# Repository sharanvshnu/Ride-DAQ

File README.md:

# RideDAQ
### Electric Scooter Ride Quality & Data Acquisition System

<p align="center">
  <b>Capture. Analyse. Predict.</b><br>
  An embedded data-acquisition platform for electric-scooter ride-quality monitoring and predictive-maintenance research.
</p>

---

## 01. Overview

**RideDAQ** is an embedded scooter-monitoring and data-acquisition system intended to capture riding dynamics, vibration, positional information and environmental parameters. The platform combines inertial sensing, GNSS, local data logging and wireless connectivity.

The longer-term objective is to study ride quality, identify abnormal vibration patterns and investigate data-driven maintenance indicators. These are development goals, not validated capabilities at this stage.

## 02. System Architecture

```mermaid
flowchart TB
    Scooter["Electric scooter"] --> Unit["RideDAQ acquisition unit"]
    subgraph Unit
      MCU["Teensy 4.0"]
      IMU["BMI323 IMU"] --> MCU
      GNSS["GP-02 GNSS"] --> MCU
      ENV["BME280"] --> MCU
      RTC["DS3231M RTC"] --> MCU
      EEPROM["I²C EEPROM — exact part to be confirmed"] <--> MCU
      MCU --> SD["MicroSD storage"]
      MCU <--> BLE["HM-10 BLE"]
    end
    BLE <--> Phone["Mobile / BLE interface"]
    SD --> Analysis["Offline data analysis"]
    Analysis --> Quality["Ride-quality assessment"]
    Analysis --> Maintenance["Predictive-maintenance research"]
```

## 03. Hardware

| Subsystem | Component / implementation | Role |
|---|---|---|
| Main controller | Teensy 4.0 | Acquisition and control |
| Inertial sensing | BMI323 6-DOF IMU breakout | Acceleration and angular velocity |
| Positioning | GP-02 GNSS module | Position and timing data |
| Environmental sensing | BME280 | Temperature, humidity and pressure |
| Real-time clock | DS3231M | Timestamp reference |
| Non-volatile memory | I²C EEPROM — part number requires reconciliation | Configuration / persistent data |
| Data logging | microSD | Local ride-data storage |
| Wireless interface | HM-10 BLE module | Wireless communication |
| Power | TPS5430 buck and LD1117S33 LDO in the current design | 5 V and 3.3 V rails |

**Important design note:** the current project files and earlier design notes disagree on the EEPROM part number (AT24CS32 versus AT24C512). The exact fitted/selected device must be confirmed before the BOM and firmware address map are treated as final.

## 04. Interfaces

| Interface | Intended peripherals |
|---|---|
| I²C | BMI323, BME280, DS3231M and EEPROM |
| SPI2 | microSD |
| UART2 | HM-10 BLE |
| UART3 | GP-02 GNSS |
| ADC | Battery-voltage sensing (planned / verify schematic connectivity) |
| GPIO | Status LEDs and GNSS PPS |

Pin assignments and hierarchical sheet connectivity remain subject to schematic review. Refer to the current KiCad design files rather than treating this summary as a pin-level sign-off.

## 05. Power Architecture

The current design uses a nominal 2S Li-ion battery input (6.0–8.4 V design range), input protection, a TPS5430-based 5 V buck stage and an LD1117S33 3.3 V LDO stage.

```mermaid
flowchart LR
  BAT["2S battery<br/>6.0–8.4 V"] --> PROT["Input protection"]
  PROT --> BUCK["TPS5430 buck<br/>5 V"]
  BUCK --> TEENSY["Teensy 4.0"]
  BUCK --> LDO["LD1117S33"]
  LDO --> RAIL["3.3 V peripherals"]
```

The power-stage component selection, low-input regulation margin, capacitor suitability, transient protection and thermal performance still require engineering verification. This block diagram describes the intended architecture, not a validated power-stage sign-off.

## 06. Development Status

| Workstream | Status |
|---|---|
| System architecture | Defined; under review |
| KiCad schematic | Created; electrical review pending |
| PCB placement / routing | In development; verify current board state |
| Firmware | Planned / in development |
| Sensor integration | Planned |
| SD data logging | Planned |
| BLE communication | Planned |
| Scooter pilot | Planned |
| Ride-quality analysis | Future work |
| Predictive-maintenance modelling | Future research |

## 07. Pilot Objectives

The initial pilot is intended to collect real-world scooter data and explore:

- Road-induced vibration characteristics
- Acceleration and movement patterns
- Ride-condition classification
- Abnormal vibration signatures
- Operational trends and potential maintenance indicators

No predictive-maintenance performance is claimed until supported by collected data and validated analysis.

## 08. Repository Structure

```text
RideDAQ/
├── v1/
│   ├── Hardware/
│   │   └── RideDAQ_KiCad/
│   │       └── RideDAQ_v1/
│   │           ├── RideDAQ_v1.kicad_pro
│   │           ├── RideDAQ_v1.kicad_sch
│   │           ├── RideDAQ_v1.kicad_pcb
│   │           ├── Sheets/
│   │           └── Libraries/
│   ├── Firmware/
│   └── Documentation/
├── README.md
└── .gitignore
```

The Firmware and Documentation directories will be populated as those workstreams mature.

## 09. Toolchain

- **Embedded platform:** Teensy 4.0
- **Firmware:** C / C++
- **Hardware design:** KiCad
- **Interfaces:** I²C, SPI, UART and BLE
- **Analysis:** Python (planned)

## 10. Engineering Gate Before PCB Release

Before manufacturing, complete and record:

1. Hierarchical schematic connectivity review.
2. Reconciliation of component MPNs, values, footprints and BOM.
3. Power-stage calculations and datasheet checks.
4. KiCad ERC with all errors reviewed.
5. Schematic-to-PCB consistency check.
6. Footprint, 3D model and connector-mechanical review.
7. PCB routing, copper zones and DRC.
8. Manufacturing-output review.

A successful Git push or a visually complete schematic/PCB is not evidence that ERC, DRC or electrical validation has passed.

---

**RideDAQ — Capture real-world data. Understand vehicle behaviour. Explore predictive maintenance.**

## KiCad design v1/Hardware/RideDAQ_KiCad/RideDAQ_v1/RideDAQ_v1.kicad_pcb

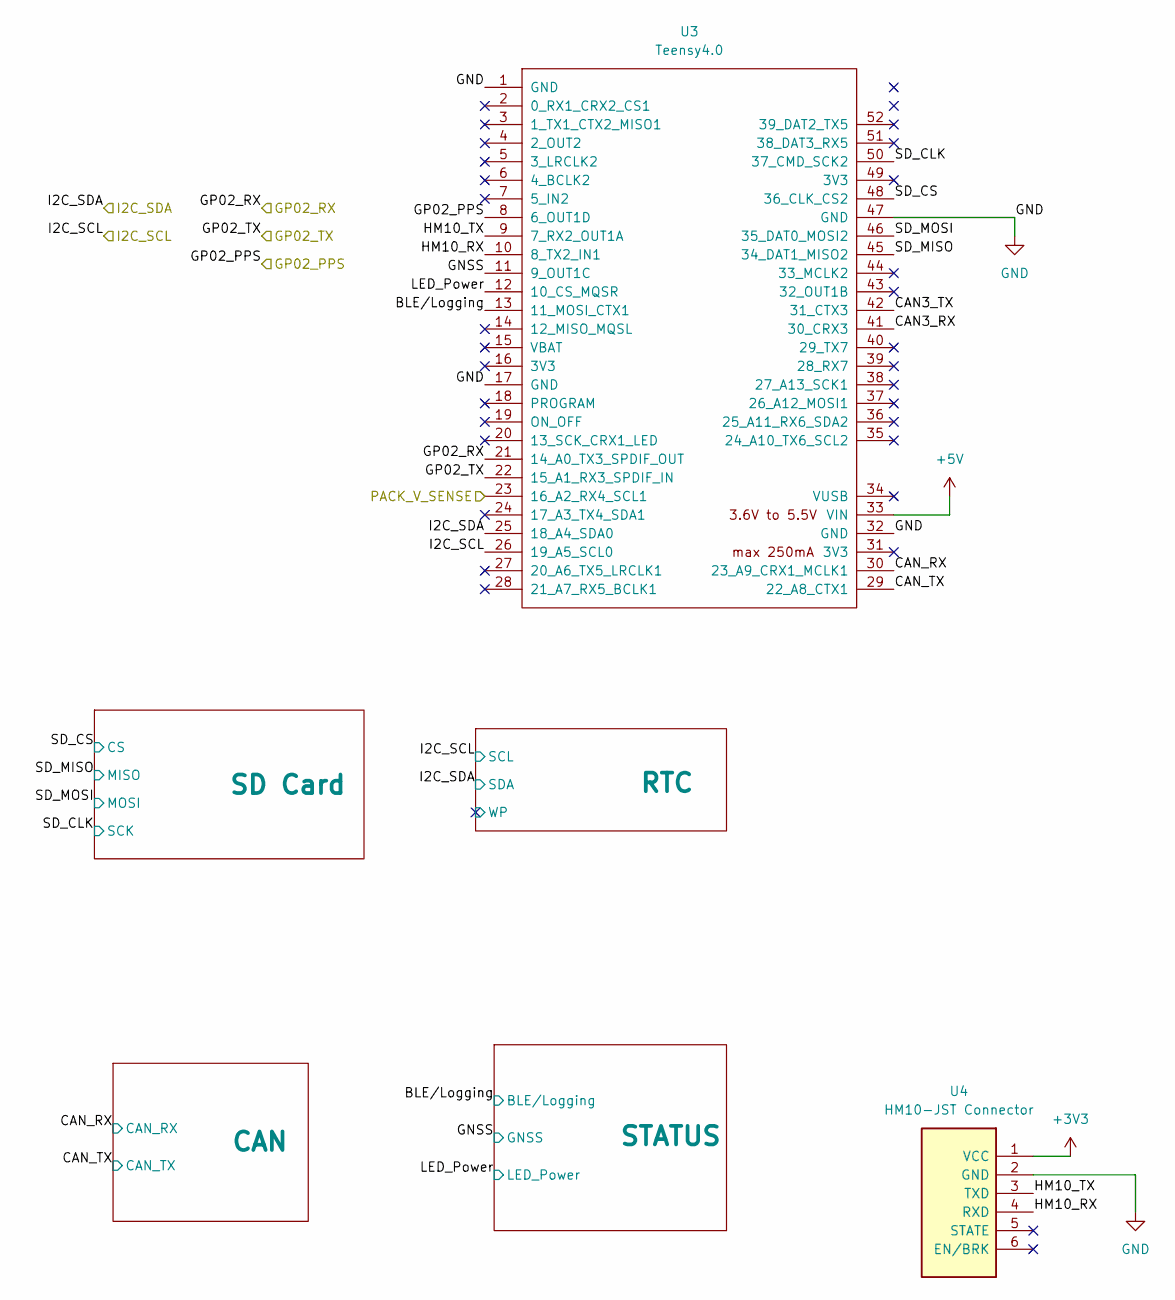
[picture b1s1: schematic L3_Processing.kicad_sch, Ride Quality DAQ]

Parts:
U3: Teensy4.0; Teensy40_All_Pins
U4: HM10-JST Connector; Molex_CLIK-Mate_502382-0670_1x06-1MP_P1.25mm_Vertical

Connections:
+3V3: U4.1 (VCC); also elsewhere on the board
+5V: U3.33 (VIN); also elsewhere on the board
/L2_Power_Conditioning/PACK_V_SENSE: U3.23 (16_A2_RX4_SCL1); also elsewhere on the board
/L3_Processing/BLE/Logging: U3.13 (11_MOSI_CTX1); also elsewhere on the board
/L3_Processing/CAN3_RX: U3.41 (30_CRX3)
/L3_Processing/CAN3_TX: U3.42 (31_CTX3)
/L3_Processing/CAN_RX: U3.30 (23_A9_CRX1_MCLK1); also elsewhere on the board
/L3_Processing/CAN_TX: U3.29 (22_A8_CTX1); also elsewhere on the board
/L3_Processing/GNSS: U3.11 (9_OUT1C); also elsewhere on the board
/L3_Processing/GP02_PPS: U3.8 (6_OUT1D); also elsewhere on the board
/L3_Processing/GP02_RX: U3.21 (14_A0_TX3_SPDIF_OUT); also elsewhere on the board
/L3_Processing/GP02_TX: U3.22 (15_A1_RX3_SPDIF_IN); also elsewhere on the board
/L3_Processing/HM10_RX: U3.10 (8_TX2_IN1), U4.4 (RXD)
/L3_Processing/HM10_TX: U3.9 (7_RX2_OUT1A), U4.3 (TXD)
/L3_Processing/I2C_SCL: U3.26 (19_A5_SCL0); also elsewhere on the board
/L3_Processing/I2C_SDA: U3.25 (18_A4_SDA0); also elsewhere on the board
/L3_Processing/LED_Power: U3.12 (10_CS_MQSR); also elsewhere on the board
/L3_Processing/SD_CLK: U3.50 (37_CMD_SCK2); also elsewhere on the board
/L3_Processing/SD_CS: U3.48 (36_CLK_CS2); also elsewhere on the board
/L3_Processing/SD_MISO: U3.45 (34_DAT1_MISO2); also elsewhere on the board
/L3_Processing/SD_MOSI: U3.46 (35_DAT0_MOSI2); also elsewhere on the board
GND: U3.1 (GND), U3.17 (GND), U3.32 (GND), U3.47 (GND), U4.2 (GND); also elsewhere on the board

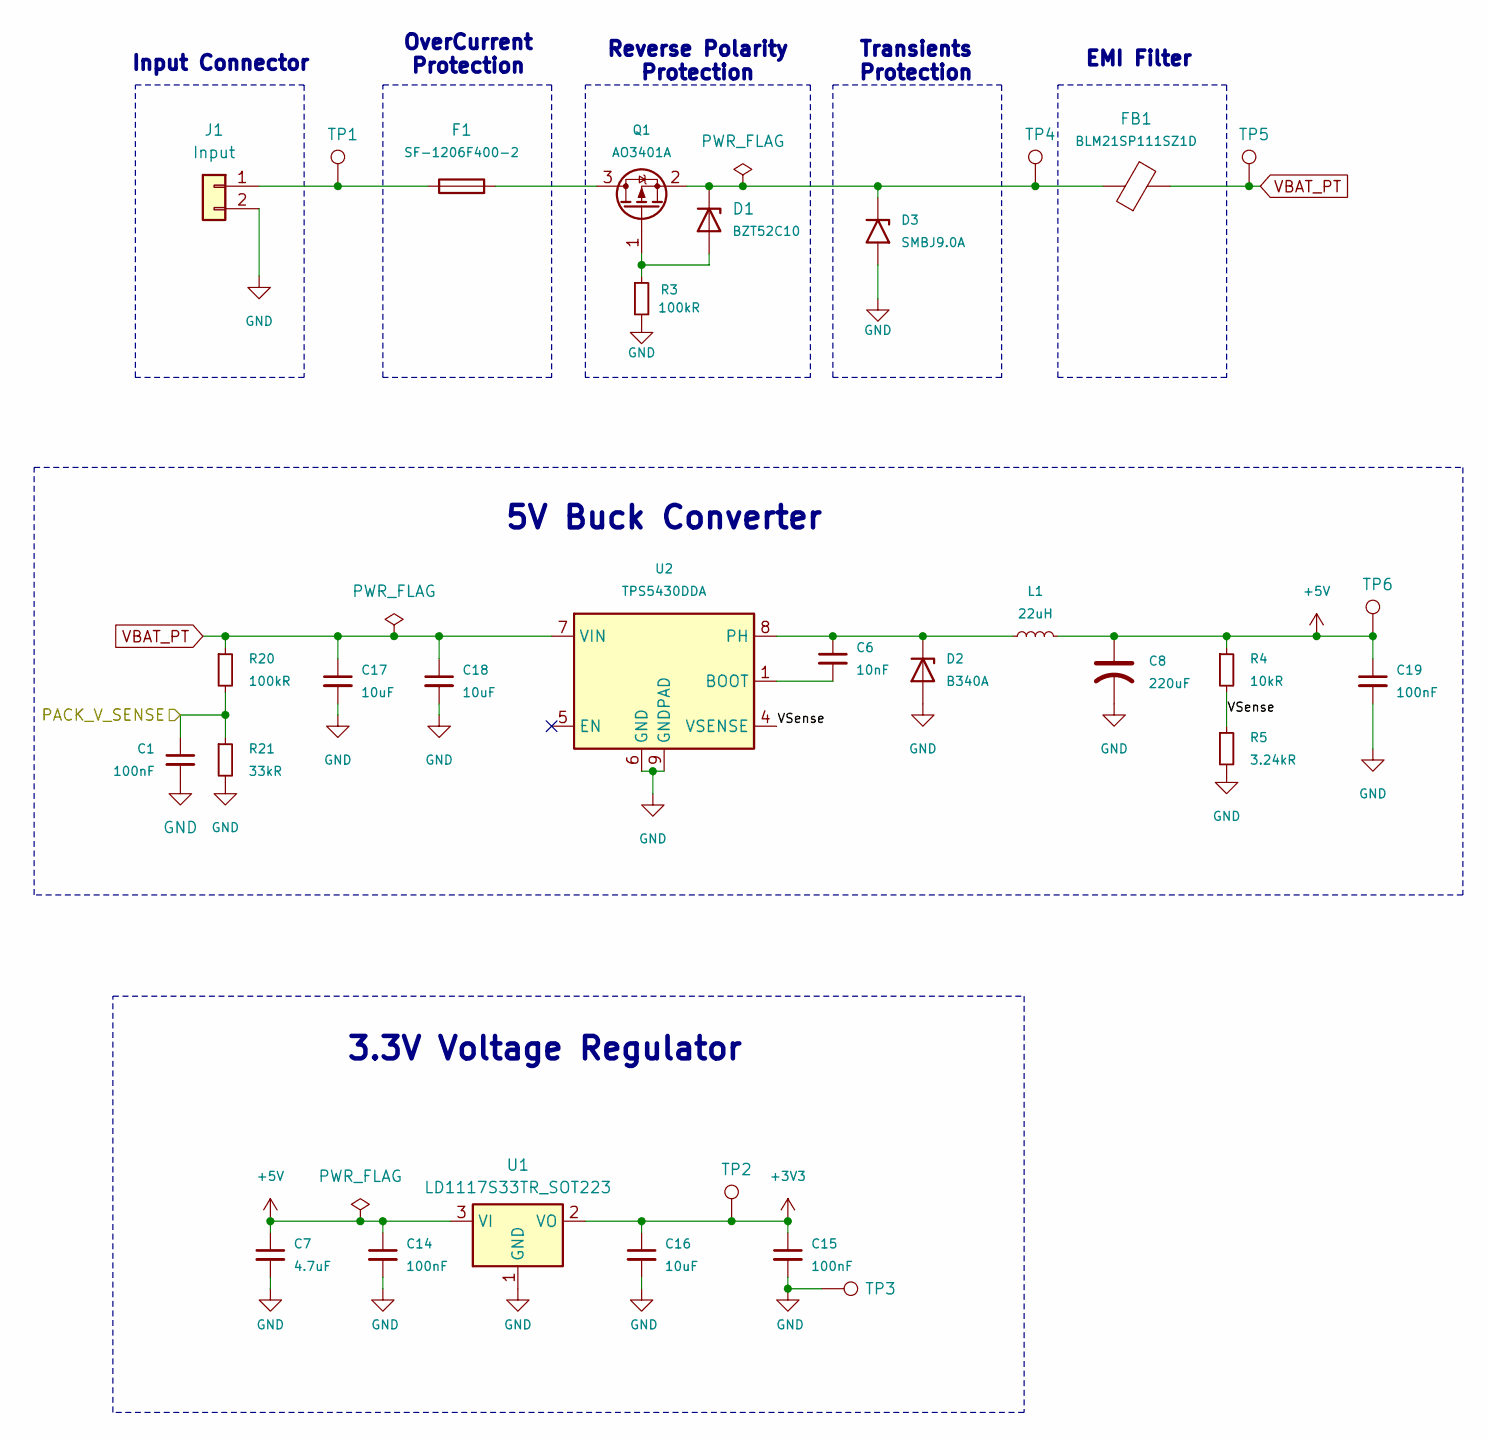
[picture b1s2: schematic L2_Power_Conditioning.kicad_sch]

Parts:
C1: 100nF; C_0805_2012Metric
C6: 10nF; C_0805_2012Metric; MPN CC0805KRX7R9BB103
C7: 4.7uF; C_0805_2012Metric; MPN TCC0805X7R475K500FT
C8: 220uF; CP_EIA-7343-31_Kemet-D; MPN UUD1C101MCL1GS
C14, C15, C19: 100nF; C_0805_2012Metric; MPN CC0805KKX7R0BB104
C16, C17, C18: 10uF; C_0805_2012Metric; MPN CL21B106KOQNNNE
D1: BZT52C10; D_SOD-123
D2: B340A; D_SMA; MPN B340A-E3/61T
D3: SMBJ9.0A; D_SMB
F1: SF-1206F400-2; Fuse_1206_3216Metric_Pad1.42x1.75mm_HandSolder
FB1: BLM21SP111SZ1D; L_0805_2012Metric
J1: Input; JST_EH_B2B-EH-A_1x02_P2.50mm_Vertical
L1: 22uH; L_12x12mm_H8mm
Q1: AO3401A; SOT-23W
R3: 100kR; R_0805_2012Metric; MPN 0805W8F1003T5E
R4: 10kR; R_0805_2012Metric; MPN RC0805FR-0710KL
R5: 3.24kR; R_0805_2012Metric; MPN 0603WAF3241T5E
R20: 100kR; R_0805_2012Metric; MPN RC0805FR-0710KL
R21: 33kR; R_0805_2012Metric; MPN 0603WAF3241T5E
TP1, TP2, TP3, TP4, TP5, TP6: TestPoint; TestPoint_Pad_D1.5mm
U1: LD1117S33TR_SOT223; SOT-223-3_TabPin2; MPN LD1117S33CTR
U2: TPS5430DDA; TI_SO-PowerPAD-8_ThermalVias

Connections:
+3V3: C15.1, C16.1, TP2.1 (1_1), U1.2 (VO); also elsewhere on the board
+5V: C7.1, C8.1, C14.1, C19.1, L1.2, R4.1, TP6.1 (1_1), U1.3 (VI); also elsewhere on the board
/L2_Power_Conditioning/PACK_V_SENSE: C1.1, R20.2, R21.1; also elsewhere on the board
/L2_Power_Conditioning/VSense: R4.2, R5.1, U2.4 (VSENSE)
GND: C1.2, C7.2, C8.2, C14.2, C15.2, C16.2, C17.2, C18.2, C19.2, D2.2 (A), D3.2 (A2), J1.2, R3.2, R5.2, R21.2, TP3.1 (1_1), U1.1 (GND), U2.6 (GND), U2.9 (GNDPAD); also elsewhere on the board
unnamed: D1.2 (A), Q1.1 (G), R3.1
unnamed: D1.1 (K), D3.1 (A1), FB1.1, Q1.2 (S), TP4.1 (1_1)
unnamed: C6.1, D2.1 (K), L1.1, U2.8 (PH)
unnamed: F1.1, J1.1, TP1.1 (1_1)
unnamed: F1.2, Q1.3 (D)
unnamed: C6.2, U2.1 (BOOT)
VBAT_PT: C17.1, C18.1, FB1.2, R20.1, TP5.1 (1_1), U2.7 (VIN)

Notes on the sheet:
Reverse Polarity Protection
Input Connector
5V Buck Converter
Transients Protection
3.3V Voltage Regulator
EMI Filter
OverCurrent Protection

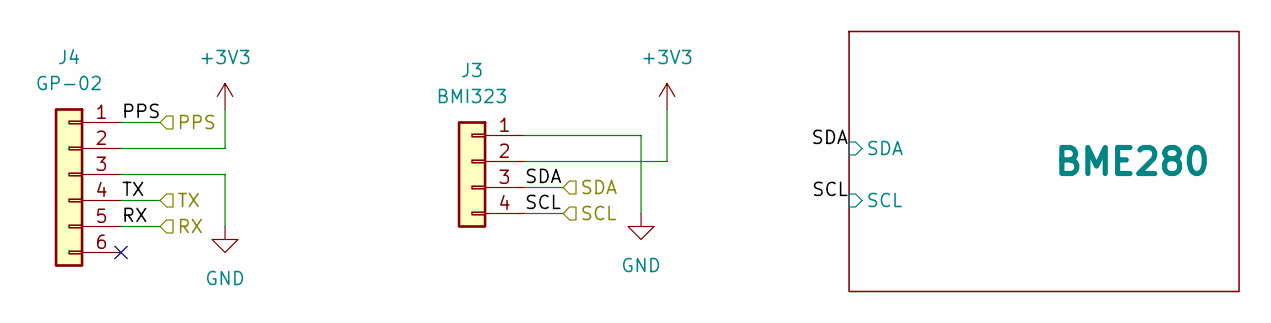
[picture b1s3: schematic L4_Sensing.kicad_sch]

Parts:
J3: BMI323; JST_SH_SM04B-SRSS-TB_1x04-1MP_P1.00mm_Horizontal
J4: GP-02; Molex_CLIK-Mate_502382-0670_1x06-1MP_P1.25mm_Vertical

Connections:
+3V3: J3.2, J4.2; also elsewhere on the board
/L3_Processing/GP02_PPS: J4.1; also elsewhere on the board
/L3_Processing/GP02_RX: J4.5; also elsewhere on the board
/L3_Processing/GP02_TX: J4.4; also elsewhere on the board
/L3_Processing/I2C_SCL: J3.4; also elsewhere on the board
/L3_Processing/I2C_SDA: J3.3; also elsewhere on the board
GND: J3.1, J4.3; also elsewhere on the board

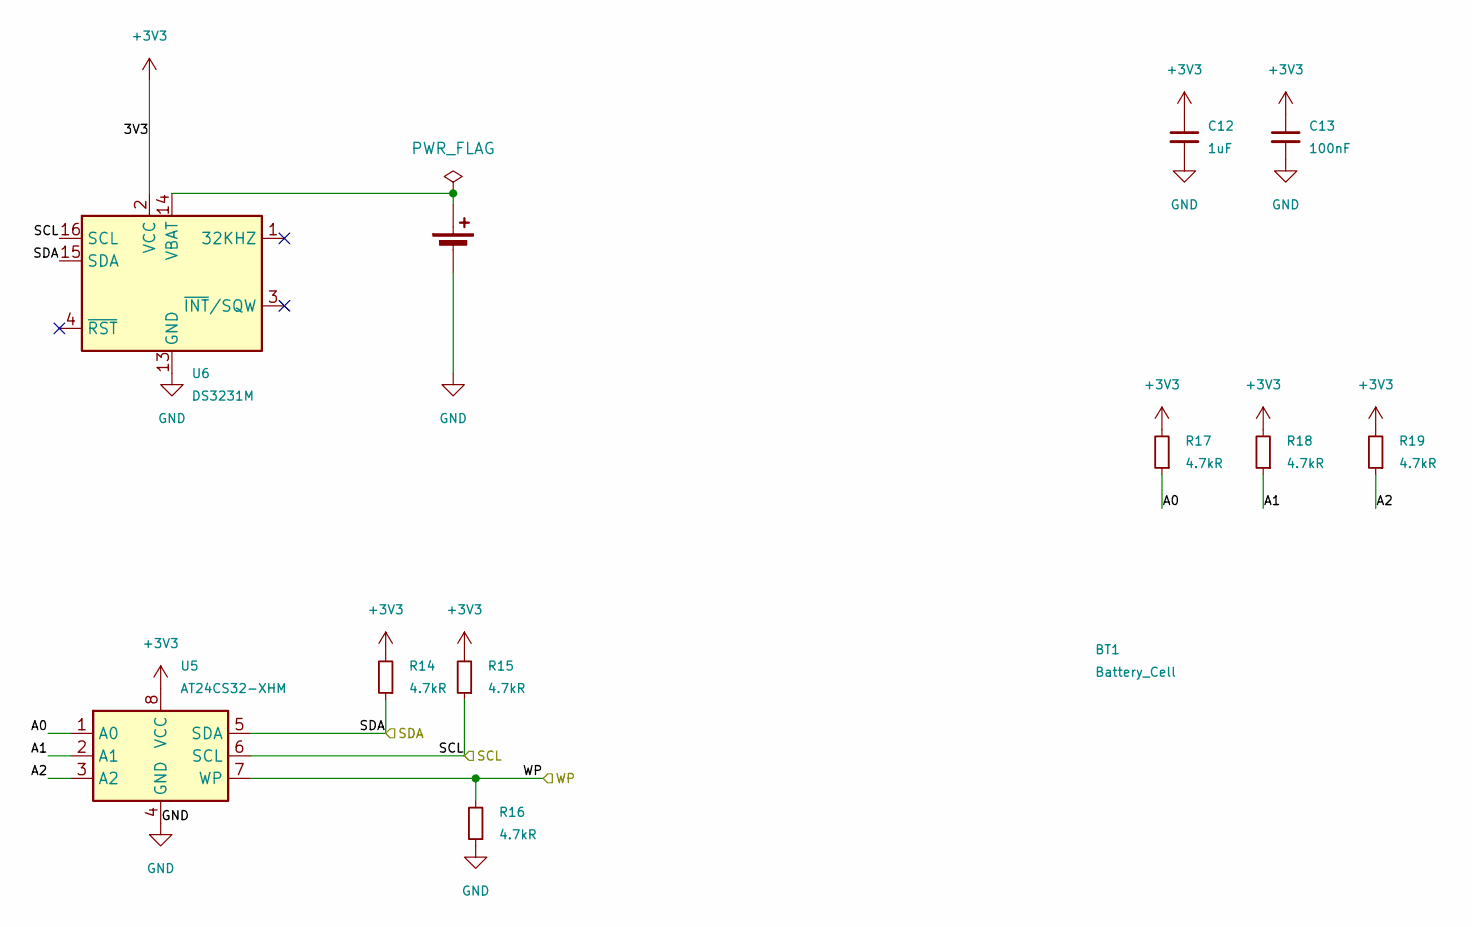
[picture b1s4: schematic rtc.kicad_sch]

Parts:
BT1: Battery_Cell; Battery_Panasonic_CR2032-HFN_Horizontal_CircularHoles
C12: 1uF; C_0805_2012Metric
C13: 100nF; C_0805_2012Metric
R14, R15, R16, R17, R18, R19: 4.7kR; R_0805_2012Metric
U5: AT24CS32-XHM; TSSOP-8_4.4x3mm_P0.65mm
U6: DS3231M; SOIC-16W_7.5x10.3mm_P1.27mm

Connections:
+3V3: C12.1, C13.1, R14.2, R15.2, R17.2, R18.2, R19.2, U5.8 (VCC), U6.2 (VCC); also elsewhere on the board
/L3_Processing/I2C_SCL: R15.1, U5.6 (SCL), U6.16 (SCL); also elsewhere on the board
/L3_Processing/I2C_SDA: R14.1, U5.5 (SDA), U6.15 (SDA); also elsewhere on the board
/L3_Processing/RTC/A0: R17.1, U5.1 (A0)
/L3_Processing/RTC/A1: R18.1, U5.2 (A1)
/L3_Processing/RTC/A2: R19.1, U5.3 (A2)
/L3_Processing/RTC/WP: R16.2, U5.7 (WP)
GND: BT1.2 (-), C12.2, C13.2, R16.1, U5.4 (GND), U6.5 (GND), U6.6 (GND), U6.7 (GND), U6.8 (GND), U6.9 (GND), U6.10 (GND), U6.11 (GND), U6.12 (GND), U6.13 (GND); also elsewhere on the board
unnamed: BT1.1 (+), U6.14 (VBAT)

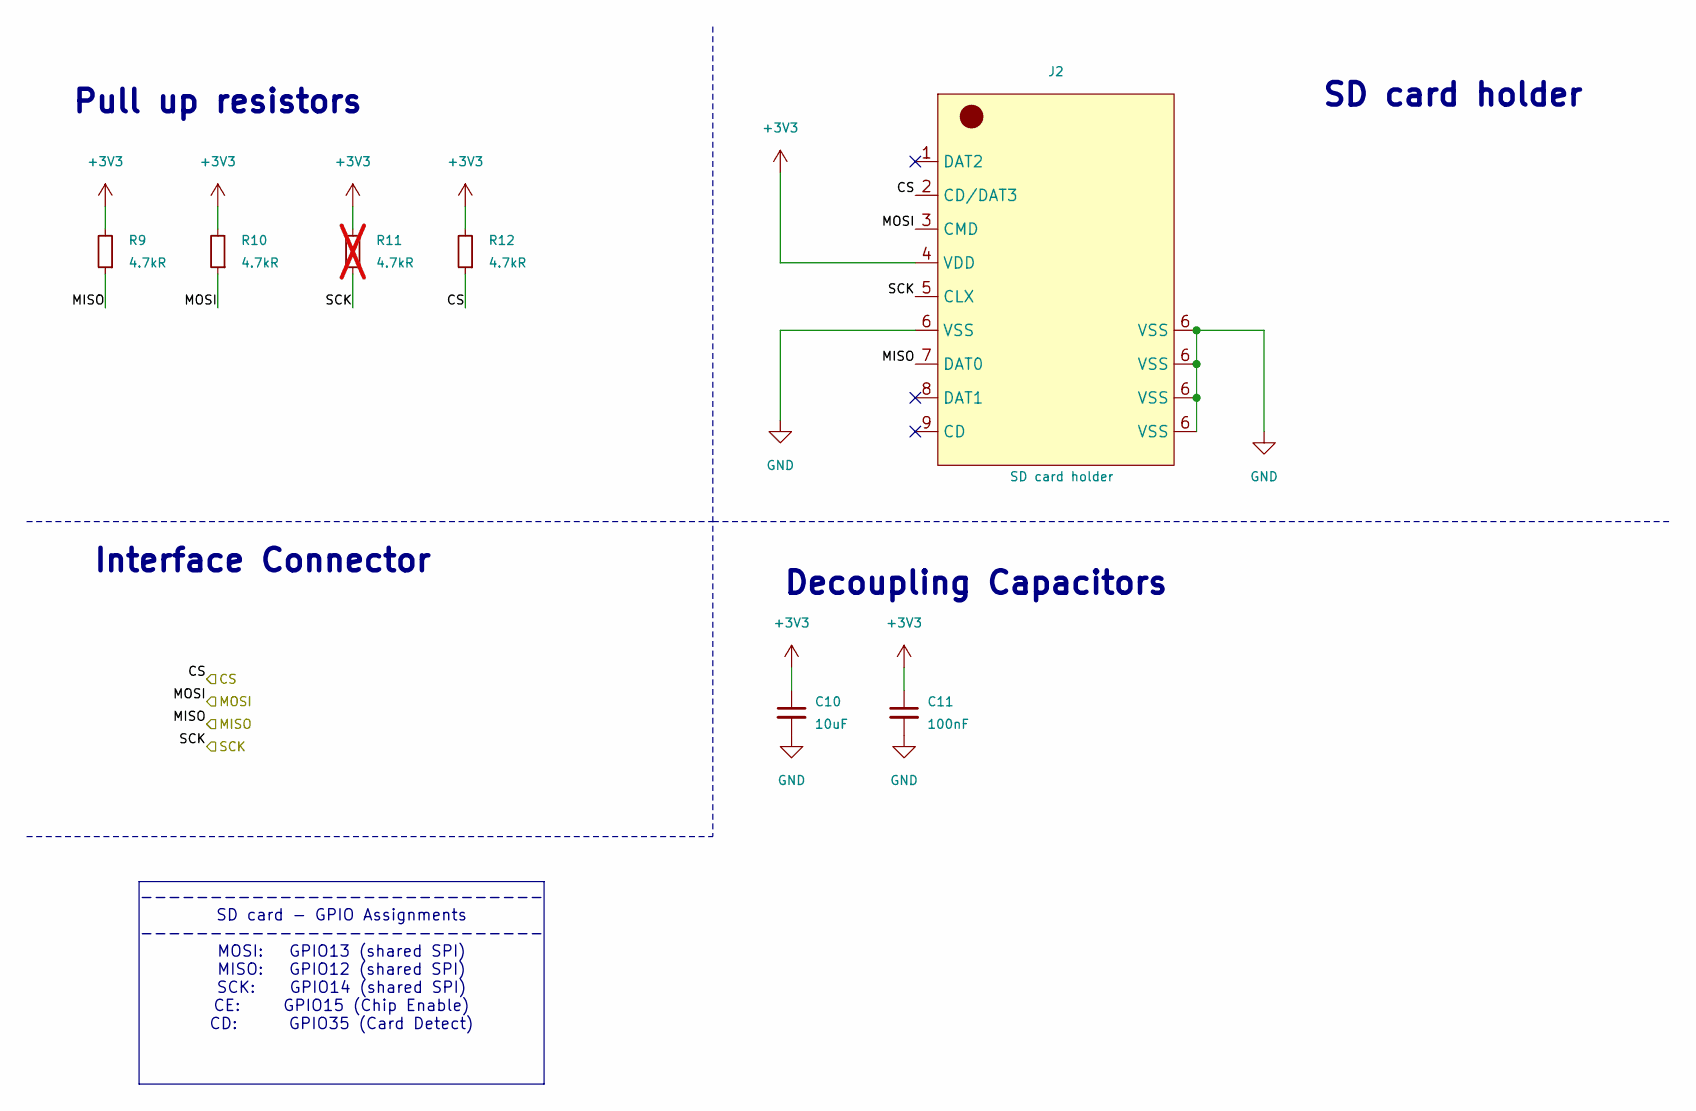
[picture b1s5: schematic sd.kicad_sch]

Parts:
C10: 10uF; C_0805_2012Metric
C11: 100nF; C_0805_2012Metric
J2: SD card holder; J_SD_Card-micro_socket_A
R9, R10, R12: 4.7kR; R_0805_2012Metric
R11: 4.7kR; R_0805_2012Metric; not fitted

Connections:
+3V3: C10.1, C11.1, J2.4 (VDD), R9.2, R10.2, R11.2, R12.2; also elsewhere on the board
/L3_Processing/SD_CLK: J2.5 (CLX), R11.1; also elsewhere on the board
/L3_Processing/SD_CS: J2.2 (CD/DAT3), R12.1; also elsewhere on the board
/L3_Processing/SD_MISO: J2.7 (DAT0), R9.1; also elsewhere on the board
/L3_Processing/SD_MOSI: J2.3 (CMD), R10.1; also elsewhere on the board
GND: C10.2, C11.2, J2.6 (VSS); also elsewhere on the board

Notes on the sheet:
SD card holder
Decoupling Capacitors
Pull up resistors
Interface Connector
----------------------------- SD card - GPIO Assignments ----------------------------- MOSI: GPIO13 (shared SPI) MISO: GPIO12 (shared SPI) SCK: GPIO14 (shared SPI) CE: GPIO15 (Chip Enable) CD: GPIO35 (Card Detect)

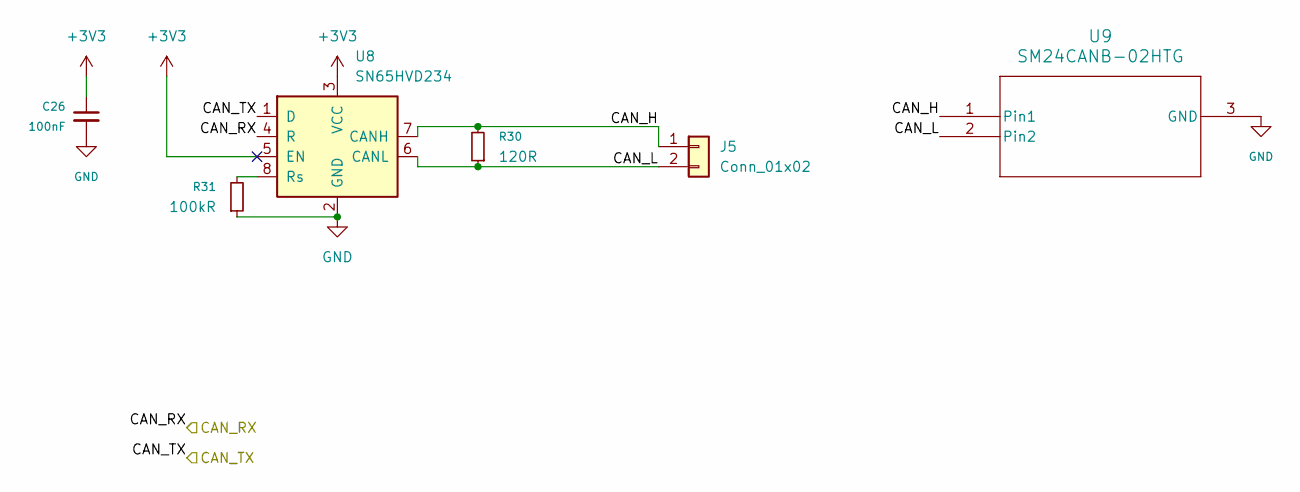
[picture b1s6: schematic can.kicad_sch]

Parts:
C26: 100nF; C_0805_2012Metric
J5: Conn_01x02; JST_EH_B2B-EH-A_1x02_P2.50mm_Vertical
R30: 120R; R_0805_2012Metric
R31: 100kR; R_0805_2012Metric
U8: SN65HVD234; SOIC-8_3.9x4.9mm_P1.27mm
U9: SM24CANB-02HTG; SOT-23W

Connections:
+3V3: C26.1, U8.3 (VCC), U8.5 (EN); also elsewhere on the board
/L3_Processing/CAN Transceiver/CAN_H: J5.1, R30.2, U8.7 (CANH), U9.1 (Pin1)
/L3_Processing/CAN Transceiver/CAN_L: J5.2, R30.1, U8.6 (CANL), U9.2 (Pin2)
/L3_Processing/CAN_RX: U8.4 (R); also elsewhere on the board
/L3_Processing/CAN_TX: U8.1 (D); also elsewhere on the board
GND: C26.2, R31.1, U8.2 (GND), U9.3 (GND); also elsewhere on the board
unnamed: R31.2, U8.8 (Rs)

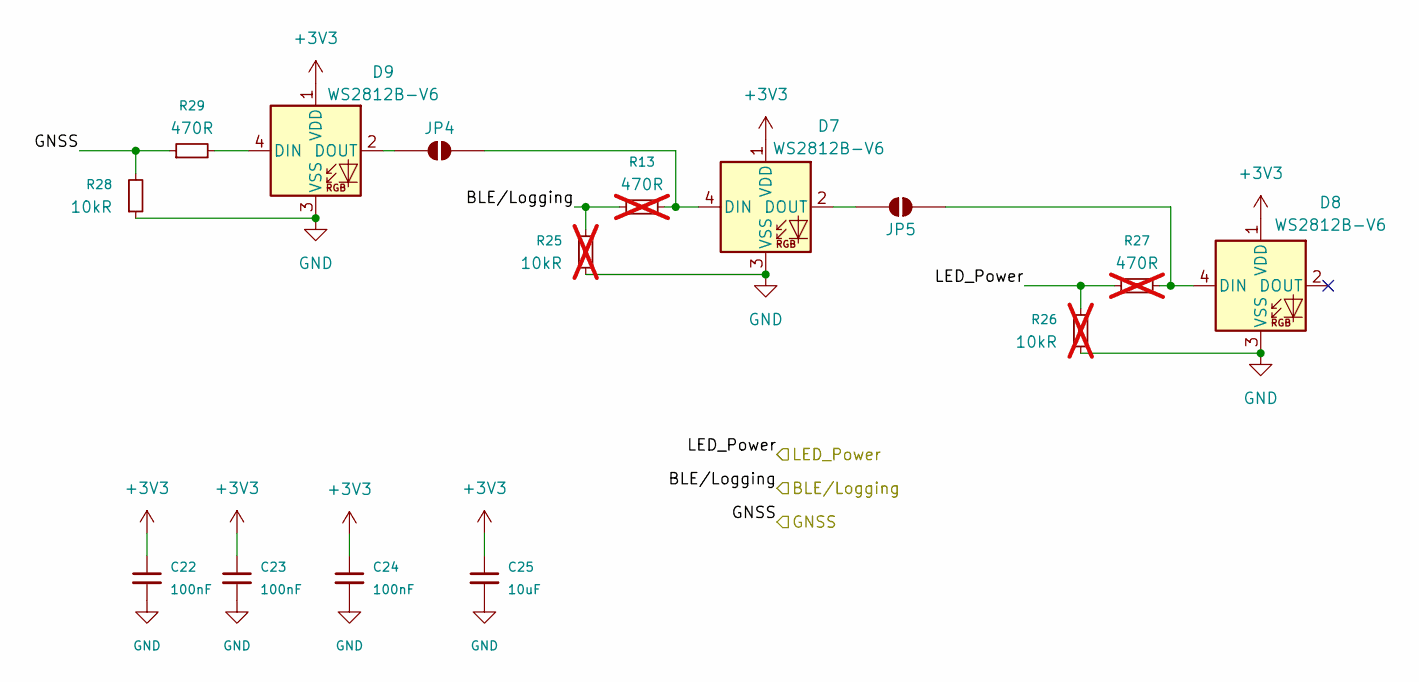
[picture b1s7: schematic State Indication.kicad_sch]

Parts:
C22, C23, C24: 100nF; C_0805_2012Metric
C25: 10uF; C_0805_2012Metric
D7, D8, D9: WS2812B-V6; LED_WS2812B_PLCC4_5.0x5.0mm_P3.2mm
JP4, JP5: SolderJumper_2_Open; SolderJumper-2_P1.3mm_Open_RoundedPad1.0x1.5mm
R13, R27: 470R; R_0805_2012Metric; not fitted
R25, R26: 10kR; R_0805_2012Metric; not fitted
R28: 10kR; R_0805_2012Metric
R29: 470R; R_0805_2012Metric

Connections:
+3V3: C22.1, C23.1, C24.1, C25.1, D7.1 (VDD), D8.1 (VDD), D9.1 (VDD); also elsewhere on the board
/L3_Processing/BLE/Logging: R13.1, R25.2; also elsewhere on the board
/L3_Processing/GNSS: R28.2, R29.1; also elsewhere on the board
/L3_Processing/LED_Power: R26.2, R27.1; also elsewhere on the board
GND: C22.2, C23.2, C24.2, C25.2, D7.3 (VSS), D8.3 (VSS), D9.3 (VSS), R25.1, R26.1, R28.1; also elsewhere on the board
unnamed: D7.4 (DIN), JP4.2 (B), R13.2
unnamed: D7.2 (DOUT), JP5.2 (B)
unnamed: D8.4 (DIN), JP5.1 (A), R27.2
unnamed: D9.4 (DIN), R29.2
unnamed: D9.2 (DOUT), JP4.1 (A)

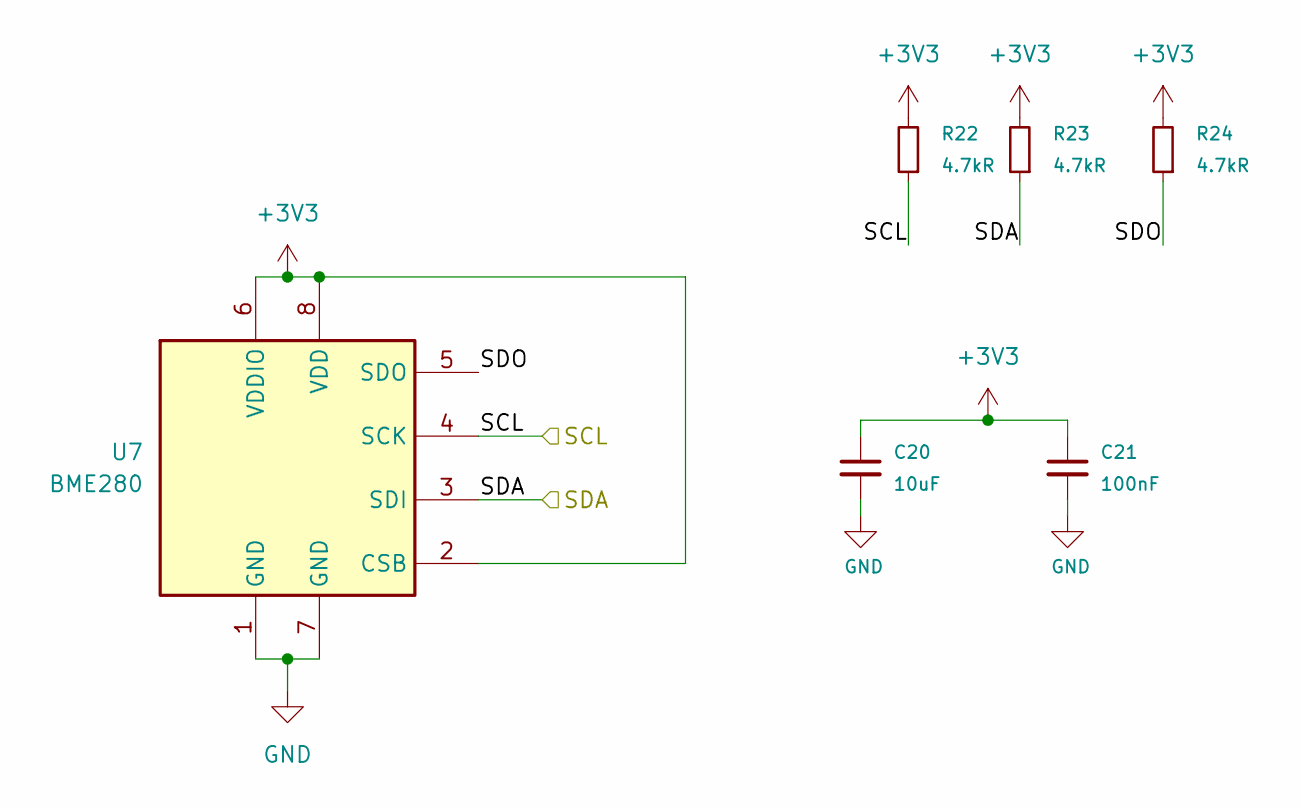
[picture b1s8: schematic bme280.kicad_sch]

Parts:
C20: 10uF; C_0805_2012Metric; MPN CL21B106KOQNNNE
C21: 100nF; C_0805_2012Metric; MPN CC0805KKX7R0BB104
R22, R23, R24: 4.7kR; R_0805_2012Metric
U7: BME280; Bosch_LGA-8_2.5x2.5mm_P0.65mm_ClockwisePinNumbering

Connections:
+3V3: C20.1, C21.1, R22.2, R23.2, R24.2, U7.2 (CSB), U7.6 (VDDIO), U7.8 (VDD); also elsewhere on the board
/L3_Processing/I2C_SCL: R22.1, U7.4 (SCK); also elsewhere on the board
/L3_Processing/I2C_SDA: R23.1, U7.3 (SDI); also elsewhere on the board
/L4_Sensing/BME280/SDO: R24.1, U7.5 (SDO)
GND: C20.2, C21.2, U7.1 (GND), U7.7 (GND); also elsewhere on the board

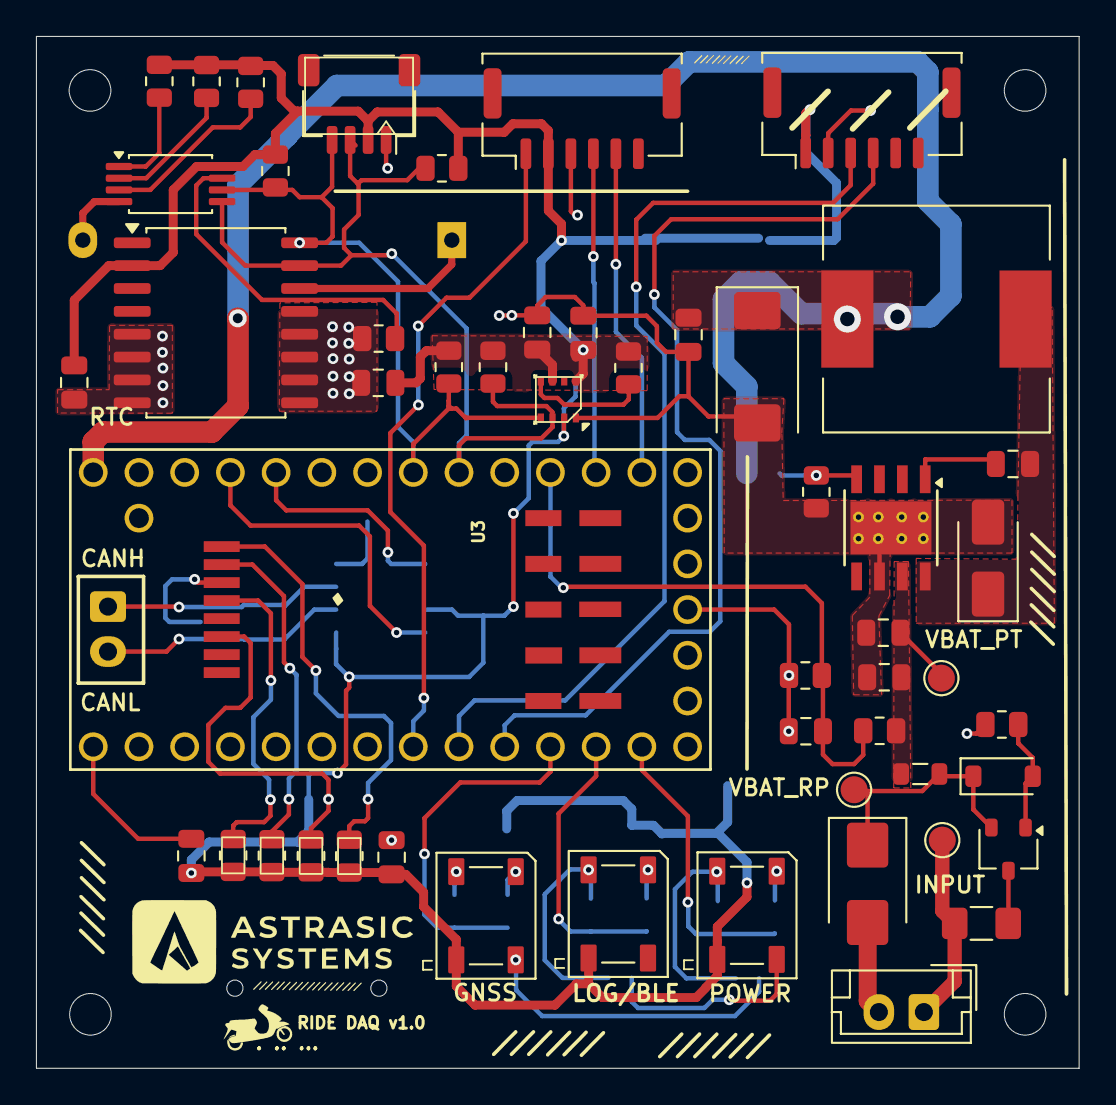
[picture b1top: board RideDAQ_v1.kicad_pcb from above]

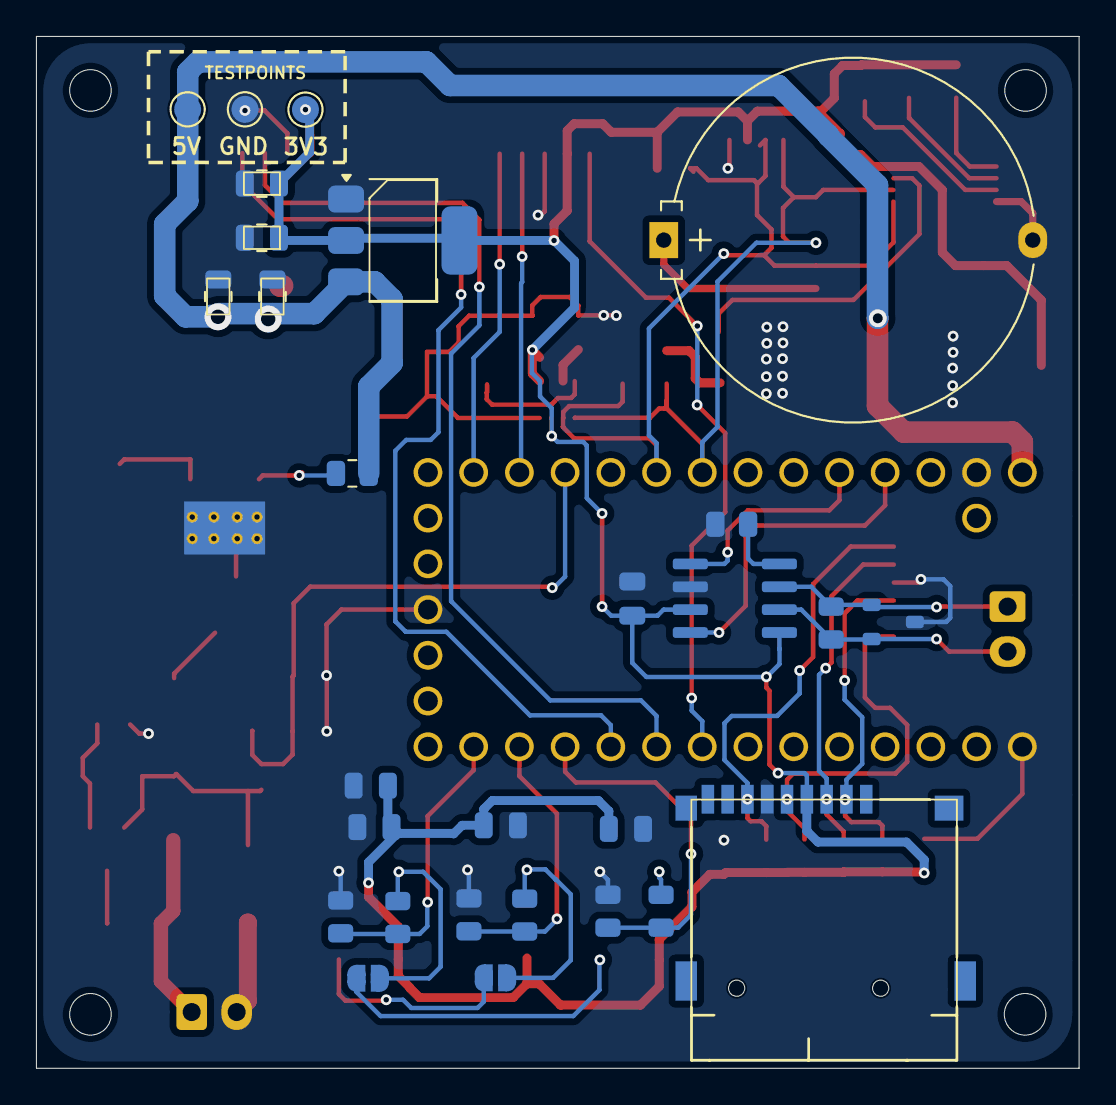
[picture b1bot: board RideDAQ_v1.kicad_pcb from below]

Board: 2 copper layers, 57.9 x 57.3 mm, 83 parts (29 on the bottom side), 42 nets.

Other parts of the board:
G1, G3: LOGO
G2: LOGO; RideDAQ_Logo_34

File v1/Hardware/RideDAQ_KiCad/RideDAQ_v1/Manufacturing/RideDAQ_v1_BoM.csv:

"Id";"Designator";"Footprint";"Quantity";"Designation";"Supplier and ref";
1;"BT1";"Battery_Panasonic_CR2032-HFN_Horizontal_CircularHoles";1;"Battery_Cell";;;
2;"C1, C11, C13, C14, C15, C19, C21";"C_0805_2012Metric";7;"100nF";;;
3;"C6";"C_0805_2012Metric";1;"10nF";;;
4;"C7";"C_0805_2012Metric";1;"4.7uF";;;
5;"C8";"CP_EIA-7343-31_Kemet-D";1;"220uF";;;
6;"C10, C16, C17, C18, C20";"C_0805_2012Metric";5;"10uF";;;
7;"C12";"C_0805_2012Metric";1;"1uF";;;
8;"D1";"D_SOD-123";1;"BZT52C10";;;
9;"D2";"D_SMA";1;"B340A";;;
10;"D3";"D_SMB";1;"SMBJ9.0A";;;
11;"D4, D5, D6";"LED_0805_2012Metric";3;"LED";;;
12;"D7";"D_SOD-123";1;"1N4148W";;;
13;"F1";"Fuse_1206_3216Metric_Pad1.42x1.75mm_HandSolder";1;"SF-1206F400-2";;;
14;"FB1";"L_0805_2012Metric";1;"BLM21SP111SZ1D";;;
15;"J1";"JST_EH_B2B-EH-A_1x02_P2.50mm_Vertical";1;"Input";;;
16;"J2";"J_SD_Card-micro_socket_A";1;"SD card holder";;;
17;"J3";"JST_SH_SM04B-SRSS-TB_1x04-1MP_P1.00mm_Horizontal";1;"BMI323";;;
18;"J4";"Molex_CLIK-Mate_502382-0670_1x06-1MP_P1.25mm_Vertical";1;"GP-02";;;
19;"L1";"L_12x12mm_H8mm";1;"22uH";;;
20;"Q1";"SOT-23W";1;"AO3401A";;;
21;"R3, R20";"R_0805_2012Metric";2;"100kR";;;
22;"R4";"R_0805_2012Metric";1;"10kR";;;
23;"R5";"R_0805_2012Metric";1;"3.24kR";;;
24;"R6, R7, R8";"R_0805_2012Metric";3;"470R";;;
25;"R9, R10, R11, R12, R14, R15, R16, R17, R18, R19, R22, R23, R24";"R_0805_2012Metric";13;"4.7kR";;;
26;"R13";"R_0805_2012Metric";1;"1MR";;;
27;"R21";"R_0805_2012Metric";1;"33kR";;;
28;"TP1, TP2, TP3, TP4, TP5, TP6";"TestPoint_Pad_D1.5mm";6;"TestPoint";;;
29;"U1";"SOT-223-3_TabPin2";1;"LD1117S33TR_SOT223";;;
30;"U2";"TI_SO-PowerPAD-8_ThermalVias";1;"TPS5430DDA";;;
31;"U3";"Teensy30_31_32_All_Pins";1;"Teensy4.0";;;
32;"U5";"TSSOP-8_4.4x3mm_P0.65mm";1;"AT24CS32-XHM";;;
33;"U6";"SOIC-16W_7.5x10.3mm_P1.27mm";1;"DS3231M";;;
34;"U7";"Bosch_LGA-8_2.5x2.5mm_P0.65mm_ClockwisePinNumbering";1;"BME280";;;
